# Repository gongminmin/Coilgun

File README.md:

# Coilgun

A coilgun is a type of mass driver. It contains one or more electromagnets to accelerate a ferromagnetic projectile to a high velocity. This project is a design of a toy level multi-stage coilgun. We'd like to make it easy to implement, so people can build it as a hobby project.

NOTE: Please turn on git LFS when cloning this project.

## Design

The principle of our design, and a detailed introduction of subsystems are in [Design](Doc/Design.md)

## Disclaimer

A coilgun is operated by **LETHALLY** high voltage and current. If you don't have enough knowledge and experiences on high voltage electric, please keep extreme cautions on insulation.

## Directories

* Circuit folder is the electric design of the system. The files can be open by [KiCad](https://kicad-pcb.org/)
* Doc folder contains some documents

## License

Coilgun is distributed under the terms of MIT License. See [LICENSE](LICENSE) for details.

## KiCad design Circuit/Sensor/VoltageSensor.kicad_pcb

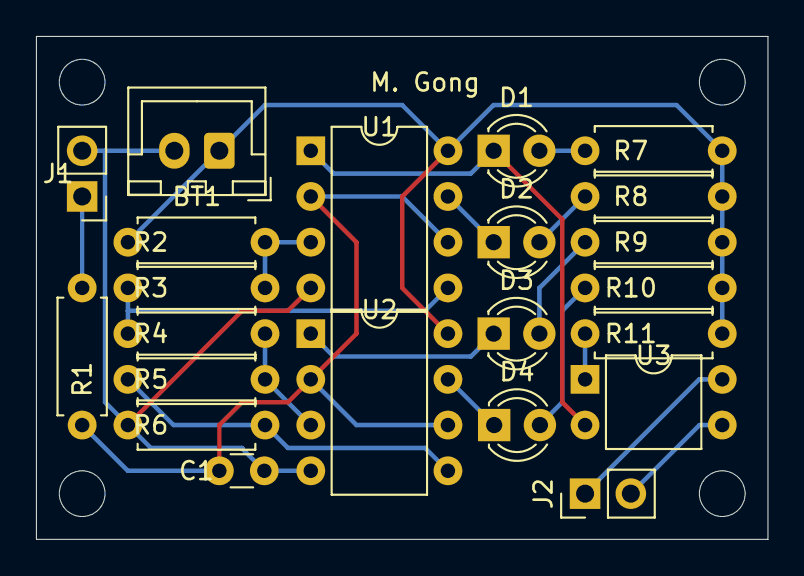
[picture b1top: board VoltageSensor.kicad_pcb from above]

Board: 2 copper layers, 40.6 x 27.9 mm, 22 parts (0 on the bottom side), 19 nets.

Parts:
BT1: 12V Battery; JST_XH_B2B-XH-A_1x02_P2.50mm_Vertical
C1: 0.1uF; C_Disc_D3.0mm_W1.6mm_P2.50mm
D1, D2, D3, D4: LED; LED_D3.0mm_FlatTop
J1: From Capacitor Bank; PinHeader_1x02_P2.54mm_Vertical
J2: To Control; PinHeader_1x02_P2.54mm_Vertical
R1, R11: 1K; R_Axial_DIN0207_L6.3mm_D2.5mm_P7.62mm_Horizontal
R2: 20K; R_Axial_DIN0207_L6.3mm_D2.5mm_P7.62mm_Horizontal
R3, R4, R5, R6: 4.7K; R_Axial_DIN0207_L6.3mm_D2.5mm_P7.62mm_Horizontal
R7, R8, R9, R10: 2.2K; R_Axial_DIN0207_L6.3mm_D2.5mm_P7.62mm_Horizontal
U1, U2: LM393; DIP-8_W7.62mm
U3: PC817; DIP-4_W7.62mm

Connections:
+12V: BT1.1, R2.2, R7.1, R8.1, R9.1, R10.1, R11.1, U1.8, U2.8
/ControlGND: J2.2, U3.3
/ControlSignal: J2.1, U3.4
/Sensor6V: J1.1, R1.2
GND: BT1.2, C1.2, J1.2, R6.1, U1.4, U2.4
unnamed: C1.1, R1.1, U1.2, U1.6, U2.2, U2.6
unnamed: D1.1, U1.1, U3.2
unnamed: D1.2, R7.2
unnamed: D2.1, U1.7
unnamed: D2.2, R8.2
unnamed: D3.1, U2.1
unnamed: D3.2, R9.2
unnamed: D4.1, U2.7
unnamed: D4.2, R10.2
unnamed: R2.1, R3.2, U1.3
unnamed: R3.1, R4.2, U1.5
unnamed: R4.1, R5.2, U2.3
unnamed: R5.1, R6.2, U2.5
unnamed: R11.2, U3.1

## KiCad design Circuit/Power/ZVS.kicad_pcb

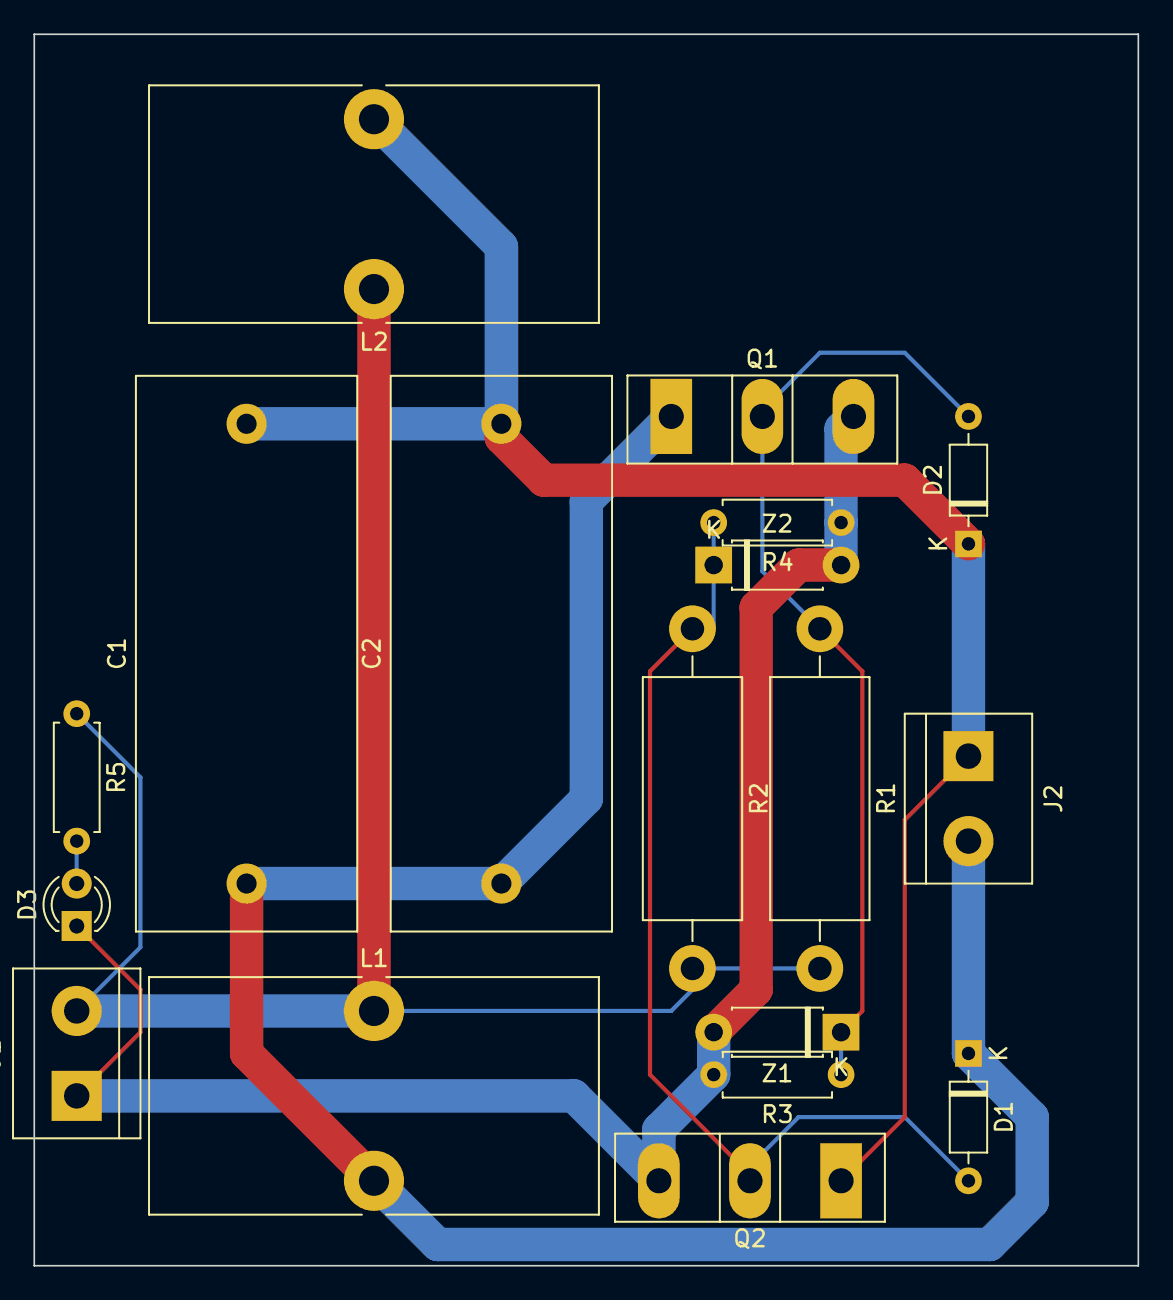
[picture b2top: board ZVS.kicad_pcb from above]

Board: 2 copper layers, 66.0 x 73.7 mm, 18 parts (0 on the bottom side), 7 nets.

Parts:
C1, C2: MKP 0.33uF; C_Rect_L33.0mm_W13.0mm_P27.50mm_MKS4
D1, D2: FR107; D_DO-35_SOD27_P7.62mm_Horizontal
D3: LED; LED_D3.0mm_FlatTop
J1: 12V DC in; TerminalBlock_bornier-2_P5.08mm
J2: Output; TerminalBlock_bornier-2_P5.08mm
L1, L2: 100uH; L_Toroid_Vertical_L26.7mm_W14.0mm_P10.16mm_Pulse_D
Q1, Q2: IRFP250; TO-247-3_Vertical
R1, R2: 470 2W; R_Axial_DIN0614_L14.3mm_D5.7mm_P20.32mm_Horizontal
R3, R4: 10K; R_Axial_DIN0207_L6.3mm_D2.5mm_P7.62mm_Horizontal
R5: 2.2K; R_Axial_DIN0207_L6.3mm_D2.5mm_P7.62mm_Horizontal
Z1, Z2: 1N4742; D_DO-41_SOD81_P7.62mm_Horizontal

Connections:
/DCInput+: J1.2, L1.1, L2.1, R1.2, R2.2, R5.1
/DCInput-: D3.1, J1.1, Q1.3, Q2.3, R3.2, R4.1, Z1.2, Z2.2
/Output+: C1.1, C2.1, D1.1, J2.2, L1.2, Q1.1
/Output-: C1.2, C2.2, D2.1, J2.1, L2.2, Q2.1
unnamed: D1.2, Q2.2, R2.1, R4.2, Z2.1
unnamed: D2.2, Q1.2, R1.1, R3.1, Z1.1
unnamed: D3.2, R5.2

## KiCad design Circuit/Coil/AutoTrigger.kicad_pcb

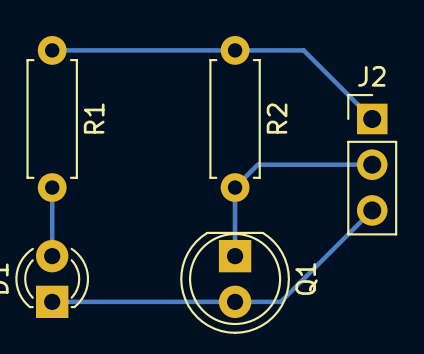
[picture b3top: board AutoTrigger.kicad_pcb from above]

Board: 2 copper layers, 5 parts (0 on the bottom side), 4 nets.

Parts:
D1: LED; LED_D3.0mm_FlatTop
J2: Trigger; PinHeader_1x03_P2.54mm_Vertical
Q1: BP103B; LED_D5.0mm_Clear
R1, R2: 2.2K; R_Axial_DIN0207_L6.3mm_D2.5mm_P7.62mm_Horizontal

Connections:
/Trigger+: J2.1, R1.1, R2.1
/TriggerSignal: J2.2, Q1.1, R2.2
GND: D1.1, J2.3, Q1.2
unnamed: D1.2, R1.2

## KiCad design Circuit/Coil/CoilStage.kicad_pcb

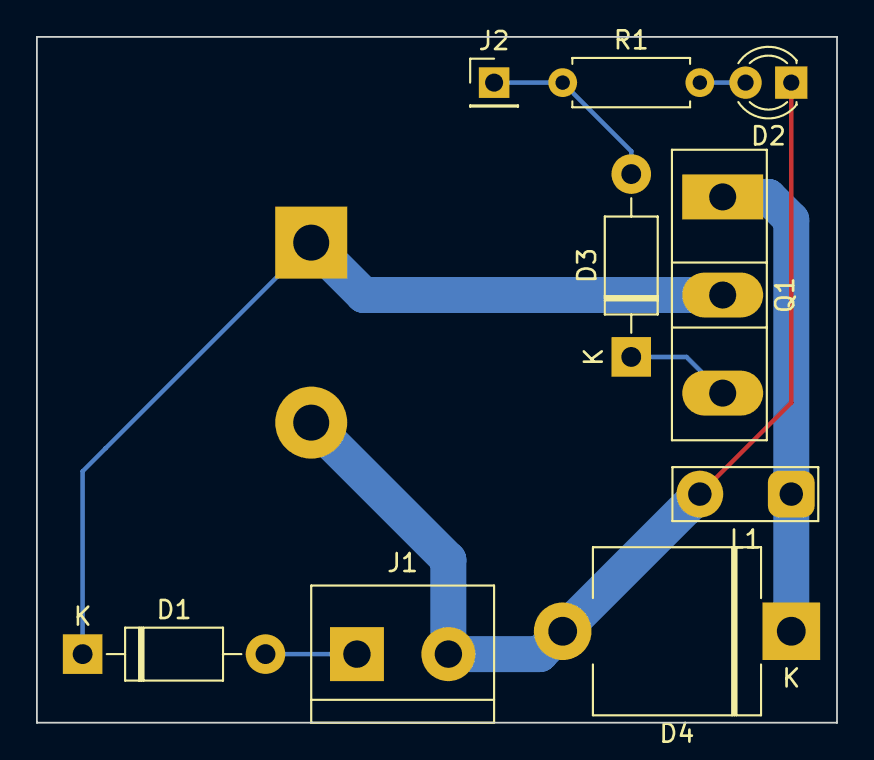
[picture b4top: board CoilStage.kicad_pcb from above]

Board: 2 copper layers, 44.4 x 38.1 mm, 10 parts (1 on the bottom side), 7 nets.

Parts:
C1: 330uF 450V; CP_Radial_D30.0mm_P10.00mm_SnapIn
D1, D3: 1N4007; D_DO-41_SOD81_P10.16mm_Horizontal
D2: LED; LED_D3.0mm_FlatTop
D4: P1000M; D_P600_R-6_P12.70mm_Horizontal
J1: Coil Power; TerminalBlock_bornier-2_P5.08mm
J2: Trigger; PinHeader_1x01_P2.54mm_Vertical
L1: Electromagnetic; TestPoint_2Pads_Pitch5.08mm_Drill1.3mm
Q1: 70PT12DS; TO-247-3_Vertical
R1: 2.2K; R_Axial_DIN0207_L6.3mm_D2.5mm_P7.62mm_Horizontal

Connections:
/CoilPower+: D1.2, J1.1
/TriggerSignal: D3.2, J2.1, R1.1
GND: C1.2, D2.1, D4.2, J1.2, L1.2
unnamed: C1.1, D1.1, Q1.2
unnamed: D2.2, R1.2
unnamed: D3.1, Q1.3
unnamed: D4.1, L1.1, Q1.1

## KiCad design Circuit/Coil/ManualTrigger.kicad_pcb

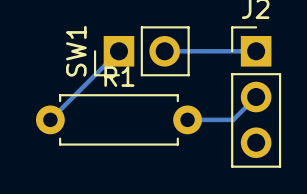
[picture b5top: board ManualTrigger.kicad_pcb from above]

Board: 2 copper layers, 3 parts (0 on the bottom side), 3 nets.

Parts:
J2: Trigger; PinHeader_1x03_P2.54mm_Vertical
R1: 2.2K; R_Axial_DIN0207_L6.3mm_D2.5mm_P7.62mm_Horizontal
SW1: SW_Push; PinHeader_1x02_P2.54mm_Vertical

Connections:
/Trigger+: J2.1, SW1.2
/TriggerSignal: J2.2, R1.2
unnamed: R1.1, SW1.1

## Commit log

2021-05-24 Init commit
2021-05-31 [Circuit] Add PCB design
2021-05-31 [Doc] Add more discussions
2021-05-31 [Circuit] File clean
2021-06-01 [Circuit] Optimize a PCB design
2021-06-03 [Circuit] Use a bigger SCR
2021-06-05 [Doc] Update the circuit image
2022-06-28 [Circuit] Update circuit files to KiCAD 6's
2022-08-25 Create n
